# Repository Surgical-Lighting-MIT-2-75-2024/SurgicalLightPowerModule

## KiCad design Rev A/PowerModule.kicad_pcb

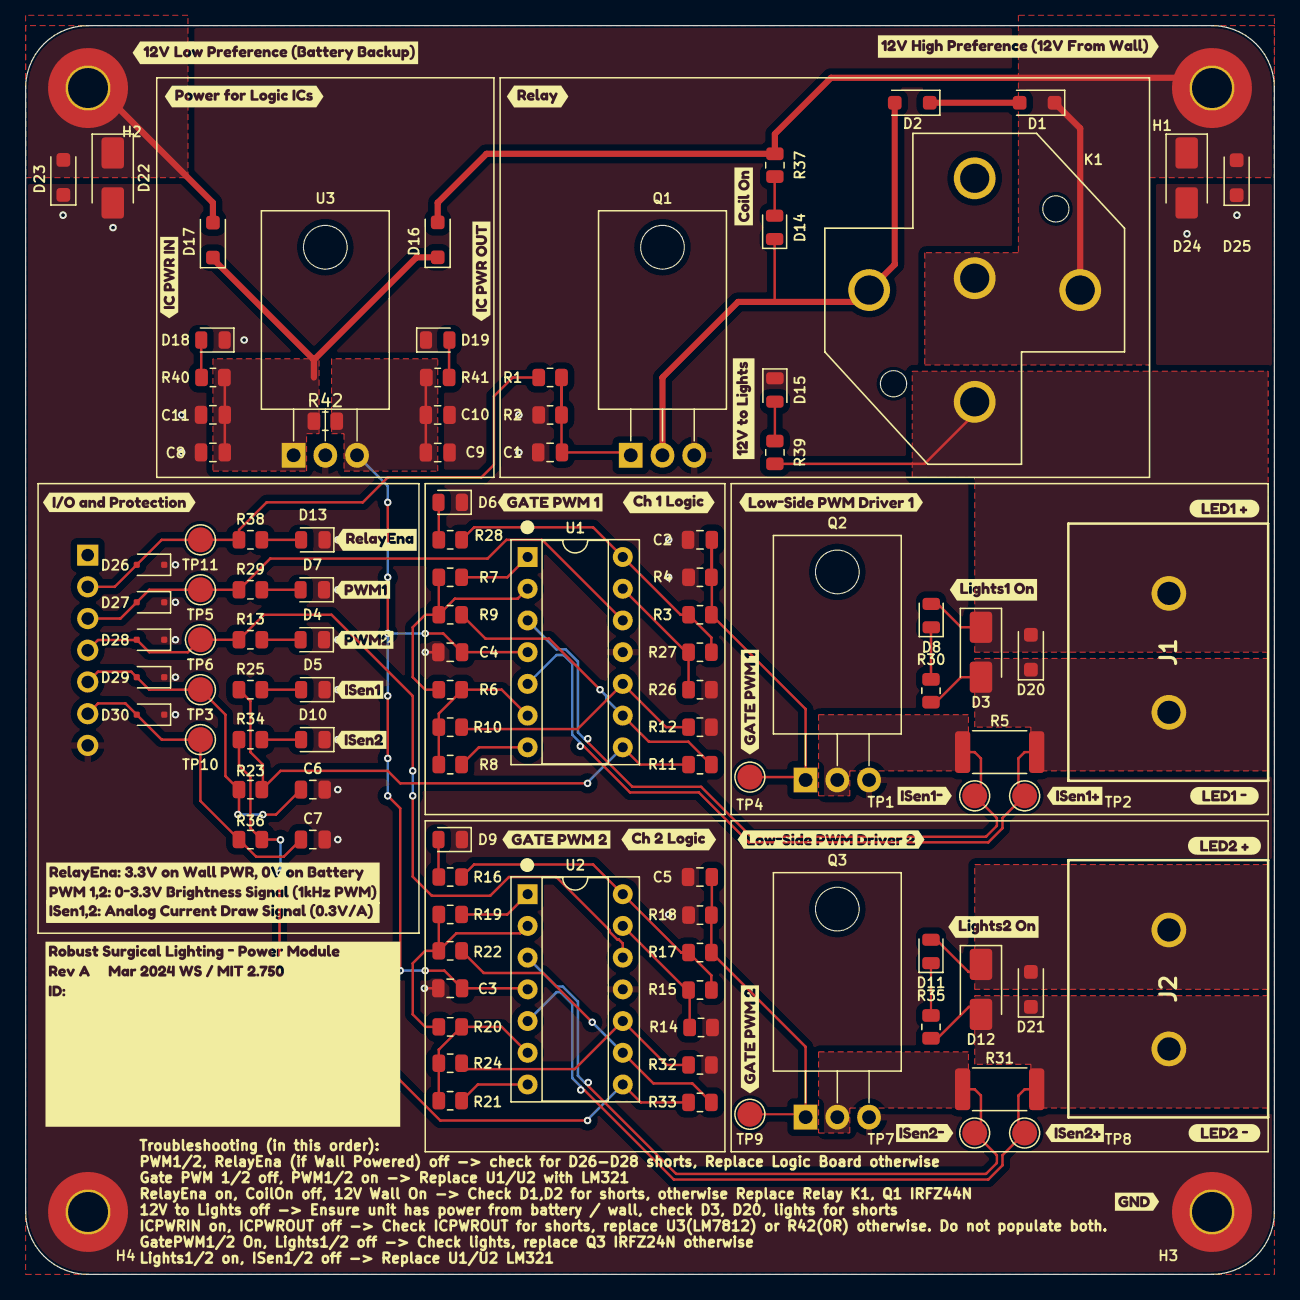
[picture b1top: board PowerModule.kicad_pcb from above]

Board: 2 copper layers, 100.0 x 100.0 mm, 144 parts (1 on the bottom side), 51 nets.

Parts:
C1, C3, C4, C8, C9, C10, C11: 1uF; C_0805_2012Metric
C2, C5, C6, C7: 10nF; C_0805_2012Metric
D1, D2, D16, D17: 1N5819W; D_SOD-123F
D3, D12, D22, D24: SMAZ15Z-13-F; D_SMA
D4, D7, D13: LED Yellow; LED_0805_2012Metric
D5, D10: LED Green; LED_0805_2012Metric
D6, D9, D14: LED Orange; LED_0805_2012Metric
D8, D11, D18, D19: LED WHITE; LED_0805_2012Metric
D15: LED Blue; LED_0805_2012Metric
D20, D21, D23, D25: SZSMF4L15CAT3G; D_SOD-123F
D26, D27, D28, D29, D30: PESD3V3L1BA,115; D_SOD-323F
H1, H2, H3, H4: M3 Hole; MountingHole_3.2mm_M3_Pad_TopBottom
J1, J2: NC6-P108-02
J3: 1x7 Socket P2.54mm; PinSocket_1x07_P2.54mm_Vertical
K1: PC792A-1C-C-12S-DN-X; TE_VCF4-1000
Q1, Q2, Q3: IRLZ44N; TO-220-3_Horizontal_TabDown
R1, R23, R36: 1K; R_0805_2012Metric
R2, R4, R18: 100K; R_0805_2012Metric
R3, R17: 100R; R_0805_2012Metric
R5, R31: 5mR 1W; R_2512_6332Metric
R6, R7, R8, R9, R10, R11, R12, R14, R15, R19, R20, R21, R22, R24, R26, R27, R32, R33: 10K; R_0805_2012Metric
R13, R16, R25, R28, R29, R34, R38, R41: 0805,1k; R_0805_2012Metric
R30, R35, R37, R39, R40: 0805,10k; R_0805_2012Metric
R42: 0805,0; R_0805_2012Metric
TP1, TP2, TP3, TP4, TP5, TP6, TP7, TP8, TP9, TP10, TP11: TestPoint_Small; TestPoint_Pad_D2.0mm
U1, U2: LM324; DIP-14_W7.62mm_Socket
U3: LM7805; TO-220-3_Horizontal_TabDown
kibuzzard-65ECAEE6: G***; kibuzzard-65ECAEE6
kibuzzard-65ECAFB8: G***; kibuzzard-65ECAFB8
kibuzzard-65ECAFEF: G***; kibuzzard-65ECAFEF
kibuzzard-65ECB1C7: G***; kibuzzard-65ECB1C7
kibuzzard-65ECB1F7, kibuzzard-65ECB1F7#2: G***; kibuzzard-65ECB1F7
kibuzzard-65ECB3CB: G***; kibuzzard-65ECB3CB
kibuzzard-65ECB3DA: G***; kibuzzard-65ECB3DA
kibuzzard-65ECB3EB: G***; kibuzzard-65ECB3EB
kibuzzard-65ECB3F2: G***; kibuzzard-65ECB3F2
kibuzzard-65ECB6CC: G***; kibuzzard-65ECB6CC
kibuzzard-65ECB6F2: G***; kibuzzard-65ECB6F2
kibuzzard-65ECB19A: G***; kibuzzard-65ECB19A
kibuzzard-65ECB040: G***; kibuzzard-65ECB040
kibuzzard-65ECB57D: G***; kibuzzard-65ECB57D
kibuzzard-65ECB58F: G***; kibuzzard-65ECB58F
kibuzzard-65ECB67C: G***; kibuzzard-65ECB67C
kibuzzard-65ECB075: G***; kibuzzard-65ECB075
kibuzzard-65ECB164: G***; kibuzzard-65ECB164
kibuzzard-65ECB203, kibuzzard-65ECB203#2: G***; kibuzzard-65ECB203
kibuzzard-65ECB213: G***; kibuzzard-65ECB213
kibuzzard-65ECB243: G***; kibuzzard-65ECB243
kibuzzard-65ECB256: G***; kibuzzard-65ECB256
kibuzzard-65ECB323: G***; kibuzzard-65ECB323
kibuzzard-65ECB342: G***; kibuzzard-65ECB342
kibuzzard-65ECB486: G***; kibuzzard-65ECB486
kibuzzard-65ECBE96: G***; kibuzzard-65ECBE96
kibuzzard-65ECDE3F: G***; kibuzzard-65ECDE3F
kibuzzard-65ECDE69: G***; kibuzzard-65ECDE69
kibuzzard-65ECDF44: G***; kibuzzard-65ECDF44
kibuzzard-65ECE287: G***; kibuzzard-65ECE287
kibuzzard-65F1E0A1: G***; kibuzzard-65F1E0A1
kibuzzard-65F778BD: G***; kibuzzard-65F778BD
kibuzzard-65F778C5: G***; kibuzzard-65F778C5
kibuzzard-65F7788D: G***; kibuzzard-65F7788D

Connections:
/12V_HighPreference: D1.1 (K), D16.2 (A), D24.1 (K), D25.2 (A2), H1.1, K1.86, K1.87A, R37.1
/12V_Lights: D3.1 (K), D8.2 (A), D11.2 (A), D12.1 (K), D20.2 (A2), D21.2 (A2), J1.1, J2.1, K1.30, R39.1
/12V_LowPreference: D17.2 (A), D22.1 (K), D23.2 (A2), H2.1, K1.87
/CurrentSenseCh1: C6.1, D29.2 (A2), J3.5, R23.2, TP3.1
/CurrentSenseCh2: C7.1, D30.2 (A2), J3.6, R36.2, TP10.1
/ISen1_unfilt: R11.2, R23.1, R25.1, U1.8
/ISen2_unfilt: R33.2, R34.1, R36.1, U2.8
/ISense1_N: Q2.2 (D), R5.2, TP1.1, U1.3 (+)
/ISense1_P: D3.2 (A), D20.1 (A1), J1.2, R5.1, R30.2, TP2.1, U1.5 (+)
/ISense2_N: Q3.2 (D), R31.2, TP7.1, U2.3 (+)
/ISense2_P: D12.2 (A), D21.1 (A1), J2.2, R31.1, R35.2, TP8.1, U2.5 (+)
/OpAmpPWR: C3.1, C4.1, C9.1, C10.1, R41.1, R42.2, U1.4 (V+), U2.4 (V+), U3.3 (VO)
/PWM_Lights1: D27.2 (A2), J3.3, R29.1, TP5.1, U1.12 (+)
/PWM_Lights2: D28.2 (A2), J3.4, R13.1, TP6.1, U2.12 (+)
/RELAY_COIL_N: D2.2 (A), D14.1 (K), K1.85, Q1.2 (D)
/RelayFETGate: C1.1, Q1.1 (G), R1.2, R2.1
/RelaySelectHighPreference: D26.2 (A2), J3.2, R1.1, R38.1, TP11.1
/VIN_OPA_PWR: C8.1, C11.1, D16.1 (K), D17.1 (K), R40.1, R42.1, U3.1 (VI)
GND: C1.2, C2.2, C3.2, C4.2, C5.2, C6.2, C7.2, C8.2, C9.2, C10.2, C11.2, D4.1 (K), D5.1 (K), D6.1 (K), D7.1 (K), D9.1 (K), D10.1 (K), D13.1 (K), D15.1 (K), D18.1 (K), D19.1 (K), D22.2 (A), D23.1 (A1), D24.2 (A), D25.1 (A1), D26.1 (A1), D27.1 (A1), D28.1 (A1), D29.1 (A1), D30.1 (A1), H3.1, H4.1, J3.7, Q1.3 (S), Q2.3 (S), Q3.3 (S), R2.2, R4.2, R12.1, R14.2, R18.2, R26.2, R32.1, U1.11 (V-), U2.11 (V-), U3.2 (GND)
unnamed: D1.2 (A), D2.1 (K)
unnamed: D4.2 (A), R13.2
unnamed: D5.2 (A), R25.2
unnamed: D6.2 (A), R28.2
unnamed: D7.2 (A), R29.2
unnamed: D8.1 (K), R30.1
unnamed: D9.2 (A), R16.2
unnamed: D10.2 (A), R34.2
unnamed: D11.1 (K), R35.1
unnamed: D13.2 (A), R38.2
unnamed: D14.2 (A), R37.2
unnamed: D15.2 (A), R39.2
unnamed: D18.2 (A), R40.2
unnamed: D19.2 (A), R41.2
unnamed: C2.1, Q2.1 (G), R3.2, R4.1, TP4.1
unnamed: C5.1, Q3.1 (G), R17.2, R18.1, TP9.1
unnamed: R7.1, U1.1
unnamed: R8.2, U1.7
unnamed: R15.2, R16.1, R17.1, U2.14
unnamed: R19.1, U2.1
unnamed: R21.2, U2.7
unnamed: R3.1, R27.2, R28.1, U1.14
unnamed: R6.1, R7.2, R9.1, U1.2 (-)
unnamed: R6.2, R8.1, R10.2, U1.6 (-)
unnamed: R10.1, R12.2, U1.10 (+)
unnamed: R9.2, R11.1, U1.9 (-)
unnamed: R26.1, R27.1, U1.13 (-)
unnamed: R19.2, R20.1, R22.1, U2.2 (-)
unnamed: R20.2, R21.1, R24.2, U2.6 (-)
unnamed: R24.1, R32.2, U2.10 (+)
unnamed: R22.2, R33.1, U2.9 (-)
unnamed: R14.1, R15.1, U2.13 (-)

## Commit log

2024-03-02 Started schematic capture
2024-03-04 added simulation stuff
2024-03-09 Added all schematic parts, started layout
2024-03-09 laid out pcb
2024-03-10 cleaned up routing
2024-03-17 added documentation for troubleshooting
2024-03-20 Moved around stuff
2024-03-25 updated screw terminal
